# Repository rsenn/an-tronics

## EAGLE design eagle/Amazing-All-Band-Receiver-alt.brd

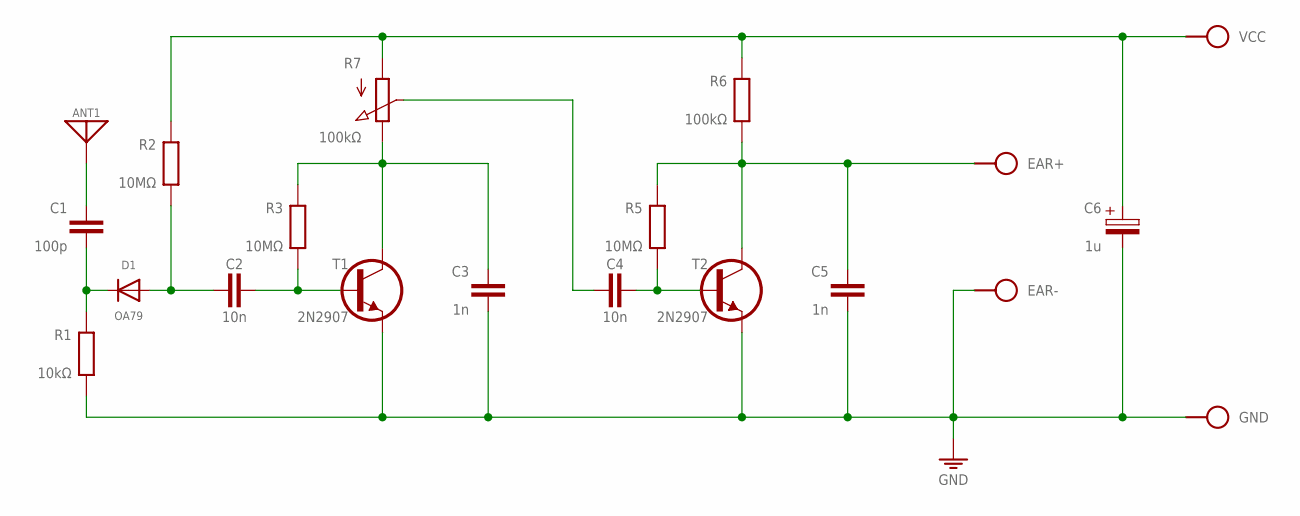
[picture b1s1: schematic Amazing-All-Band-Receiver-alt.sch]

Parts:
ANT1: ANT; SPAD
C1: 100p; C050-020X036/V
C2, C4: 10n; C050-020X036
C3, C5: 1n; C050-020X036
C6: 1u; E2,5-3
D1: OA79; DO34-7V
EAR+: SPAD
EAR-: SPAD
GND: SPAD
R1: 10kΩ; 0202/7-V
R2: 10MΩ; 0202/7
R3, R5: 10MΩ; 0202/7-V
R6: 100kΩ; 0202/7-V
R7: 100kΩ; POT
T1, T2: 2N2907; TO92
VCC: SPAD

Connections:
AC: C1.2, D1.C, R1.2
ANT: ANT1.1, C1.1
DC: C2.2, D1.A, R2.1
GND: C3.2, C5.2, C6.-, EAR-.1, GND.1, R1.1, T1.3 (E), T2.3 (E)
I1: C2.1, R3.1, T1.2 (B)
I2: C4.1, R5.1, T2.2 (B)
O1: C3.1, R3.2, R7.3 (E), T1.1 (C)
O2: C5.1, EAR+.1, R5.2, R6.1, T2.1 (C)
VCC: C6.+, R2.2, R6.2, R7.1 (A), VCC.1
VO1: C4.2, R7.2 (S)

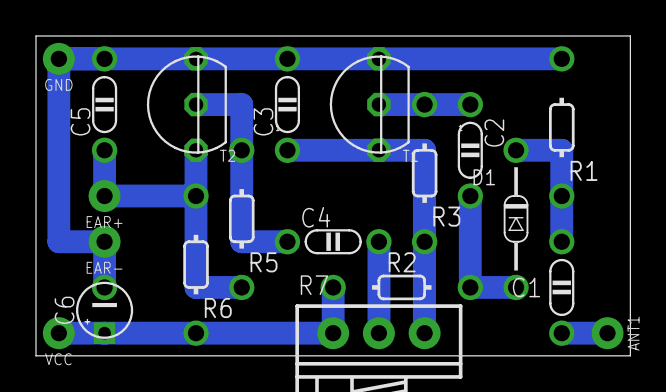
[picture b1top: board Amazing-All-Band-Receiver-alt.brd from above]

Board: 2 copper layers, 33.0 x 17.8 mm, 20 parts (0 on the bottom side), 10 nets.

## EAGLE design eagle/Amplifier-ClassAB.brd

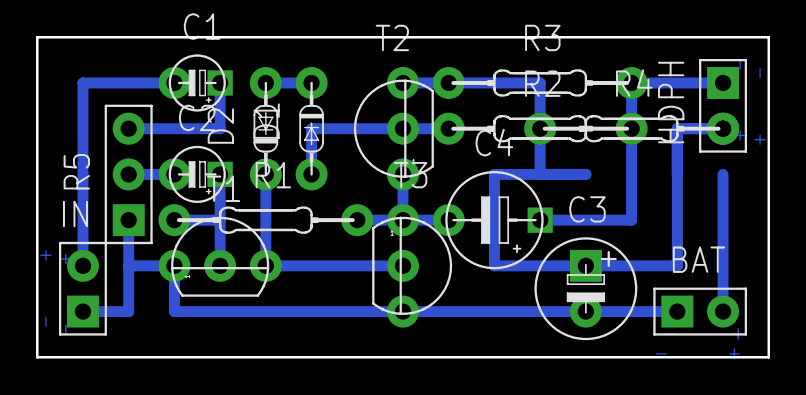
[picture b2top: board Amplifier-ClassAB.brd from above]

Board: 2 copper layers, 40.6 x 17.8 mm, 17 parts (0 on the bottom side), 12 nets.

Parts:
BAT: SPAD+-+-; SPAD+-
C1, C2: 4.7μF; E2,5-3
C3: 470μF; E2,5-6
C4: 100μF; E5-4
D1: 1N4148; DO34-5-V
D2: 1N4148; DO34-5V
HDPH: SPAD+--+; SPAD-+
IN: SPAD+--+; SPAD-+
R1: 100kΩ; 0204/10
R2: 330Ω; 0204/10
R3: 100Ω; 0204/10
R4: 27Ω; 0204/10
R5: 100kΩ; CONN-3P
T1: 2N3904; TO92
T2: 2N3904; TO92_T2
T3: 2N3906; TO92_T2

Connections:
GND: BAT.1, C3.-, IN.1, R5.1, T1.1, T3.3
unnamed: D1.A, R2.1, T2.2
unnamed: D2.C, T1.3, T3.2
unnamed: D1.C, D2.A
unnamed: C4.-, R1.2, T2.1, T3.1
unnamed: C1.+, R5.3
unnamed: C2.-, R5.2
unnamed: C2.+, R1.1, T1.2
unnamed: R3.1, T2.3
unnamed: C4.+, HDPH.1, R2.2, R3.2
unnamed: C1.-, IN.2
NET_13: HDPH.2, R4.1

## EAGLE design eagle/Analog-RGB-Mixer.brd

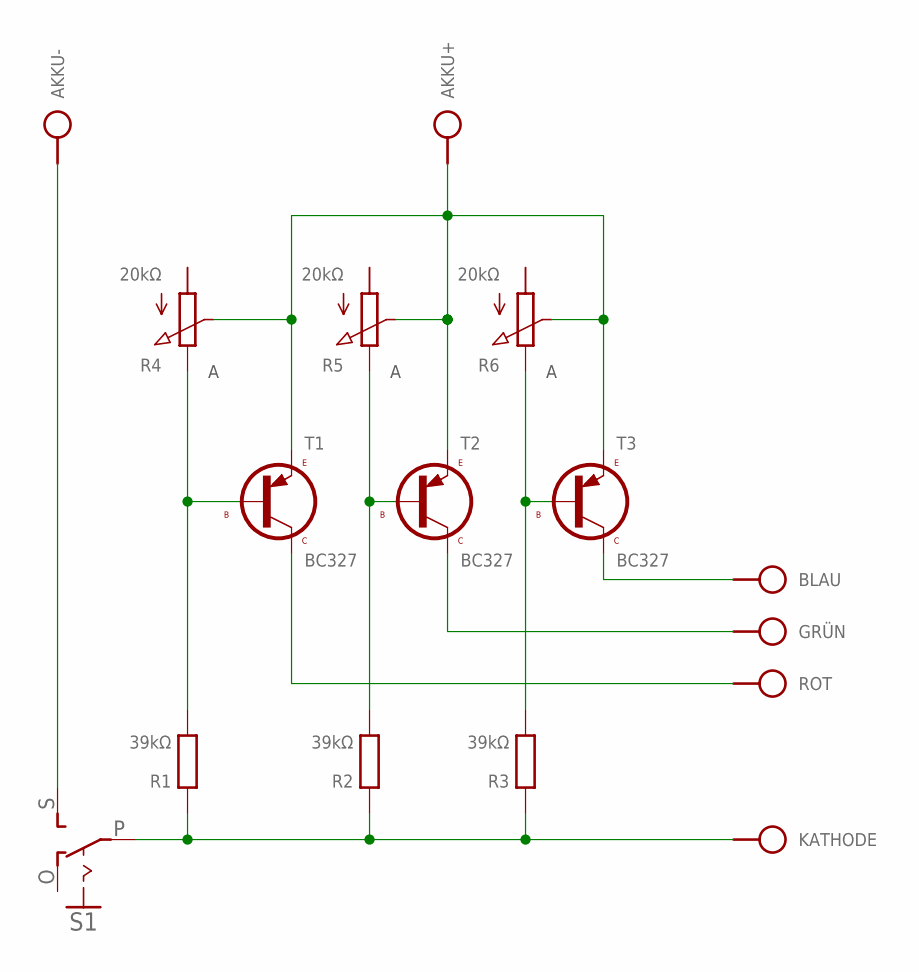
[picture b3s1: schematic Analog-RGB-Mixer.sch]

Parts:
AKKU: SPAD+--+; SPAD-+
BLAU: HPORT; SPAD
GRÜN: HPORT; SPAD
KATHODE: HPORT; SPAD
R1: 39kΩ; 0204/5
R2: 39kΩ; 0204/12-V
R3: 39kΩ; 0204/20-V
R4, R5, R6: 20kΩ; CONN-2P
ROT: HPORT; SPAD
S1: SL-SW-1P-2T-H; SLSW-1P2T-H
T1, T2, T3: BC327; TO92

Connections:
unnamed: R1.2 (1), R4.1 (A), T1.2 (B)
unnamed: R2.2 (1), R5.1 (A), T2.2 (B)
unnamed: R3.1, R6.1 (A), T3.2 (B)
unnamed: KATHODE.1, R1.1 (2), R2.1 (2), R3.2, S1.P
unnamed: AKKU.1, S1.S
unnamed: AKKU.2, R4.2 (S), R5.2 (S), R6.2 (S), T1.3 (E), T2.3 (E), T3.3 (E)
unnamed: BLAU.1, T3.1 (C)
unnamed: ROT.1, T1.1 (C)
unnamed: GRÜN.1, T2.1 (C)

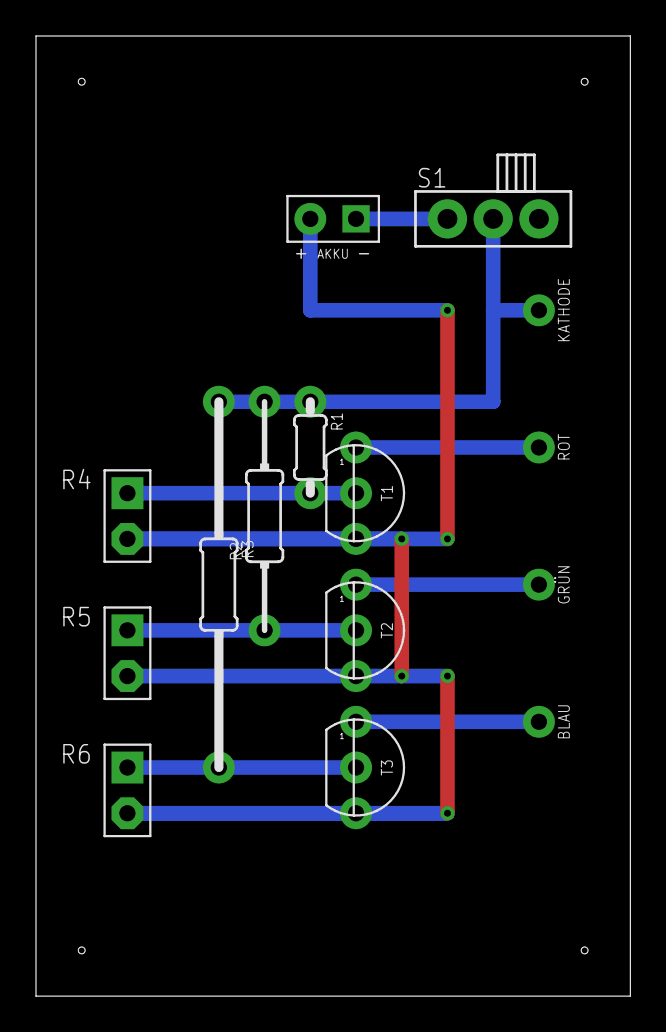
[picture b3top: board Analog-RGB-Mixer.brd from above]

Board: 2 copper layers, 33.0 x 53.3 mm, 15 parts (0 on the bottom side), 9 nets.

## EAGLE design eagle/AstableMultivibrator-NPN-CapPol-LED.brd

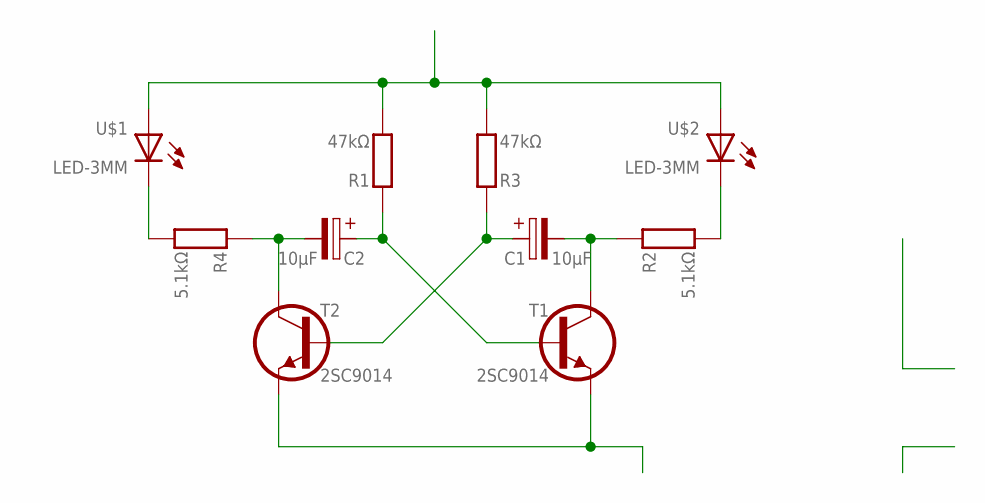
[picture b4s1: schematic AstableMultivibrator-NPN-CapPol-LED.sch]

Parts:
C1, C2: 10μF; E2,5-4
R1, R3: 47kΩ; 0202/7-V
R2, R4: 5.1kΩ; 0202/7-V
T1, T2: 2SC9014; TO92-EBC
U$1, U$2: LED-3MM; LED_3MM

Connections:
unnamed: C2.-, R4.2 (1), T2.C
unnamed: C2.+, R1.2 (1), T1.B
unnamed: C1.+, R3.2 (1), T2.B
unnamed: R1.1 (2), R3.1 (2), U$1.A, U$2.A
unnamed: T1.E, T2.E
unnamed: C1.-, R2.2 (1), T1.C
unnamed: R4.1 (2), U$1.K (C)
unnamed: R2.1 (2), U$2.K (C)

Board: 2 copper layers, 10 parts (0 on the bottom side), 8 nets, no tracks yet.

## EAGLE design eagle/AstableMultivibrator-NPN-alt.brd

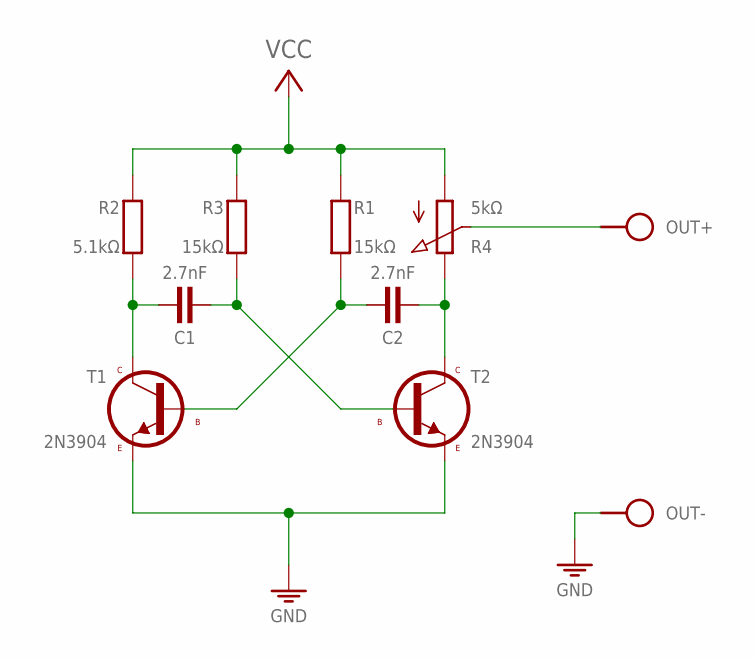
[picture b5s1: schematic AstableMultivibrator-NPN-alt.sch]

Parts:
C1, C2: 2.7nF; C0750-020X044
J1: VCC_GNDPWR-L; PWR-L
OUT: SPAD+-+-; SPAD+-
R1, R3: 15kΩ; 0204/10-V
R2: 5.1kΩ; 0204/10-V
R4: 5kΩ; POT-V
T1, T2: 2N3904; TO92

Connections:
GND: J1.1 (GND), OUT.1, T1.1 (E), T2.1 (E)
unnamed: C2.2, R4.E, T2.3 (C)
unnamed: C1.1, R2.2, T1.3 (C)
unnamed: C2.1, R1.2, T1.2 (B)
unnamed: C1.2, R3.2, T2.2 (B)
unnamed: OUT.2, R4.S
VCC: J1.2 (VCC), R1.1, R2.1, R3.1, R4.A

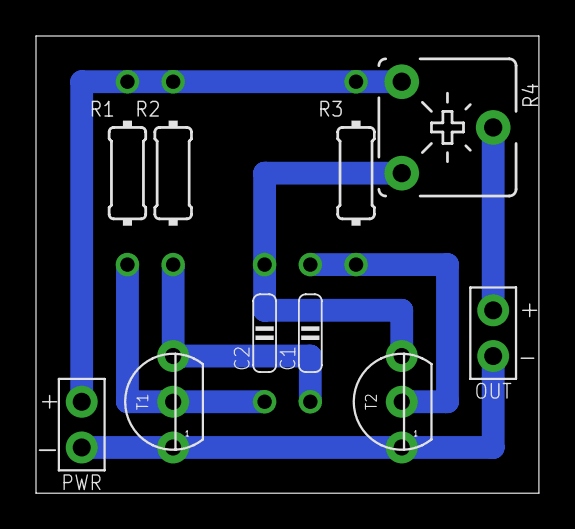
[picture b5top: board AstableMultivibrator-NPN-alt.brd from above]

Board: 2 copper layers, 27.9 x 25.4 mm, 10 parts (0 on the bottom side), 7 nets.

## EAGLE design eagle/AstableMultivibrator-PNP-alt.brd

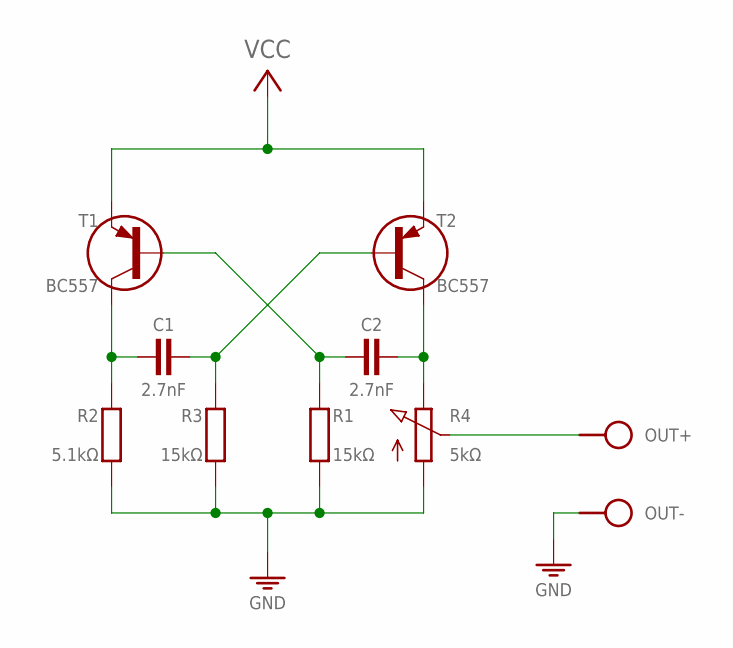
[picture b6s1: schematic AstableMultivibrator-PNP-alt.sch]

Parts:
C1, C2: 2.7nF; C0750-020X044
J1: VCC_GNDPWR-L; PWR-L
OUT: SPAD+-+-; SPAD+-
R1, R3: 15kΩ; 0202/7-V
R2: 5.1kΩ; 0202/7-V
R4: 5kΩ; POT-V
T1, T2: BC557; TO92-CBE

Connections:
GND: J1.1 (GND), OUT.1, R1.1 (2), R2.1 (2), R3.1 (2), R4.A
unnamed: C2.2, R4.E, T2.C
unnamed: C1.1, R2.2 (1), T1.C
unnamed: C2.1, R1.2 (1), T1.B
unnamed: C1.2, R3.2 (1), T2.B
unnamed: OUT.2, R4.S
VCC: J1.2 (VCC), T1.E, T2.E

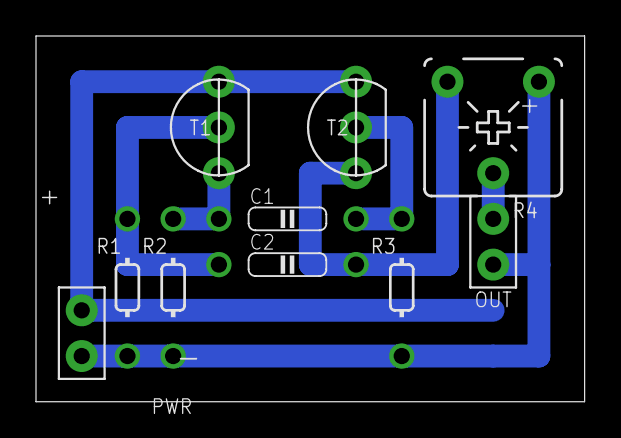
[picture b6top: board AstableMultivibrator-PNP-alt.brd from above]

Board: 2 copper layers, 30.5 x 20.3 mm, 10 parts (0 on the bottom side), 7 nets.
